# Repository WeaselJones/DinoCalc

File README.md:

DinoCalculator Version 1.0

Download updates from:
http://code.google.com/p/dinocalc/

Summary:
When I was younger I had a calculator that did not have a LCD display but instead had two LED lights, one green and one red.  You would enter a math problem with what you thought the correct answer was (for example, 12 + 12 = 24, and then press the "?" key).  If your answer was right the green LED would light up, if your answer was wrong, the red LED would light up.

This is my salute to that toy from my childhood, as well as a great way for me to engineer and program a neat little project that my preschool son can actually use to check his simple math.

This first part will document the prototype that I have built.  My first objective was to create a calculator capable of just adding and subtracting using off the shelf items.  I plan on starting with an Arduino Pro Mini for the developmental and prototype stage and once I can get most of the major bugs worked out I will then move on to a final version that has a lower cost and device count (ATmega328p on a custom PCB).  

Future objectives (not in any particular order) will be to:

1) Replace the Arduino Pro Mini board with a custom made PCB and reduce parts to a minimum to lower costs (I already have several friends wanting versions for their kids)

2) Add multiplication and division to the calculator's capabilities (low priority for me since this will involve more keys then a 4x4 matrix keypad and my son is only starting addition and subtraction right now)

3) Develop a custom keypad (maybe using tactile buttons and caps, or making my own "membrane" type keypad, or exploring "conductive" type buttons)

4) Add sound for errors or beep whenever custom keypad button is pressed

5) Develop code so that it could also be used for a "math" type game for multiple players. For example, Display a math problem and contestants enter answer on their calculators. If their answer is right, their token moves away from some peril (like a chomping dinosaur) and if wrong moves closer to peril. Loser is the one that gets eaten (chomp,chomp,chomp)

6) Make the circuit low-power for longer battery life and replace the 9V battery with two NiMH AA batteries or perhaps even a button cell rechargeable battery

7) Add a recharging circuit to recharge the rechargeable batteries from USB

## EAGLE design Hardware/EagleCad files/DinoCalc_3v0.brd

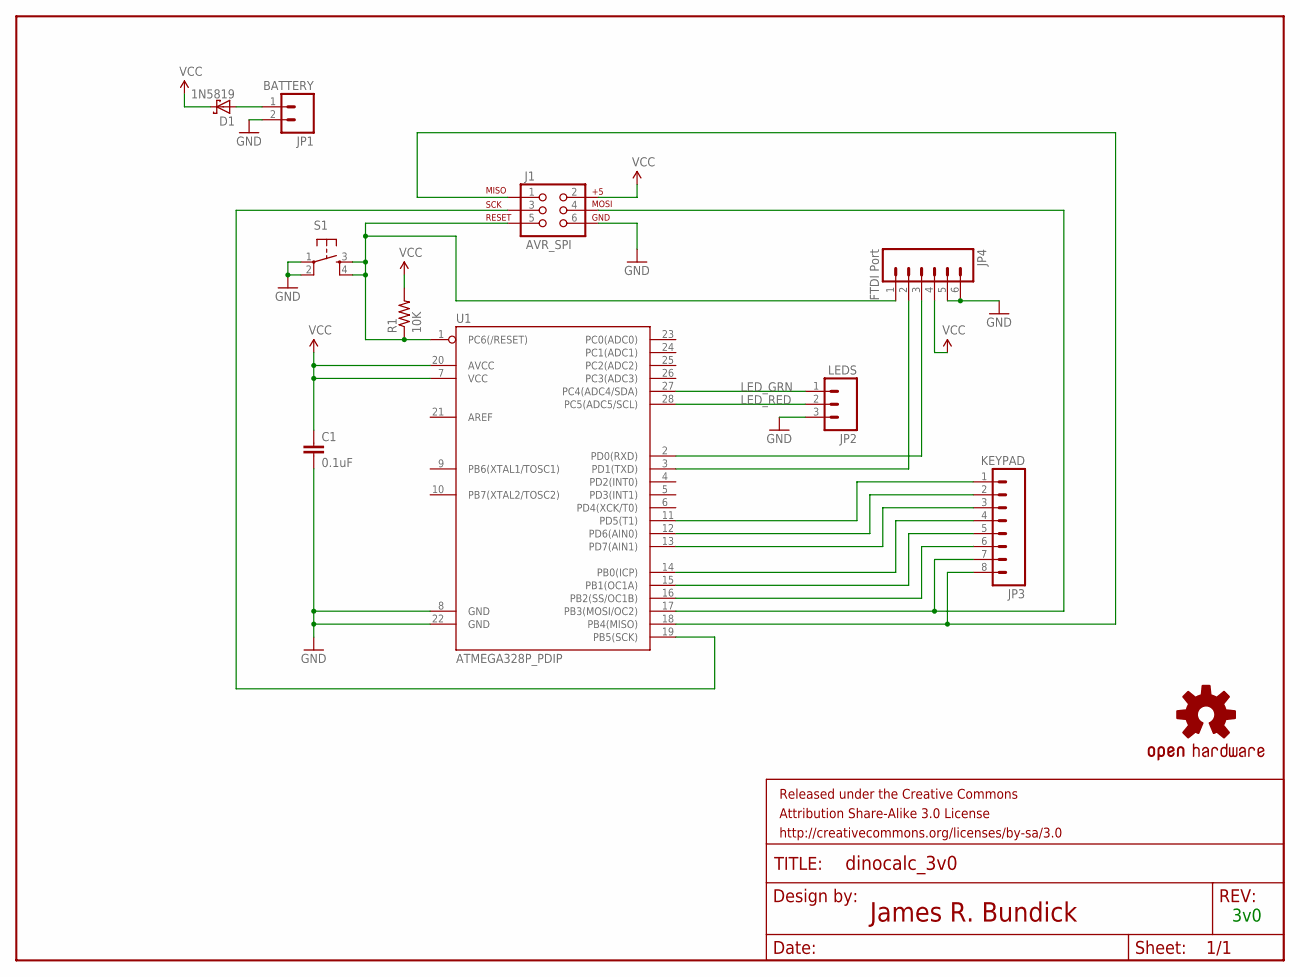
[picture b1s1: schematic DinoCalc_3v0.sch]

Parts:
C1: 0.1uF; CAP-PTH-SMALL
D1: 1N5819; CB417-15
FRAME1: FRAME-LETTER; CREATIVE_COMMONS
J1: AVR_SPI; 2X3_OFFSET
JP1: BATTERY; 1X02
JP2: LEDS; 1X03
JP3: KEYPAD; 1X08
JP4: FTDI Port; 1X06_LONGPADS
LOGO1: OSHW-LOGOL; OSHW-LOGO-L
R1: 10K; AXIAL-0.4
S1: TAC_SWITCHPTH; TACTILE-PTH
U1: ATMEGA328P_PDIP; DIL28-3

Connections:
GND: C1.2, J1.6, JP1.2, JP2.3, JP4.5, JP4.6, S1.1, S1.2, U1.8 (GND), U1.22 (GND)
LED_GRN: JP2.1, U1.27 (PC4(ADC4/SDA))
LED_RED: JP2.2, U1.28 (PC5(ADC5/SCL))
unnamed: JP4.3, U1.2 (PD0(RXD))
unnamed: JP4.2, U1.3 (PD1(TXD))
unnamed: JP3.1, U1.11 (PD5(T1))
unnamed: JP3.2, U1.12 (PD6(AIN0))
unnamed: JP3.3, U1.13 (PD7(AIN1))
unnamed: JP3.4, U1.14 (PB0(ICP))
unnamed: JP3.5, U1.15 (PB1(OC1A))
unnamed: JP3.6, U1.16 (PB2(SS/OC1B))
unnamed: J1.4, JP3.7, U1.17 (PB3(MOSI/OC2))
unnamed: J1.1, JP3.8, U1.18 (PB4(MISO))
unnamed: D1.A, JP1.1
unnamed: J1.5, JP4.1, R1.P$1 (1), S1.3, S1.4, U1.1 (PC6(/RESET))
unnamed: J1.3, U1.19 (PB5(SCK))
VCC: C1.1, D1.C, J1.2, JP4.4, R1.P$2 (2), U1.7 (VCC), U1.20 (AVCC)

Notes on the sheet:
3v0

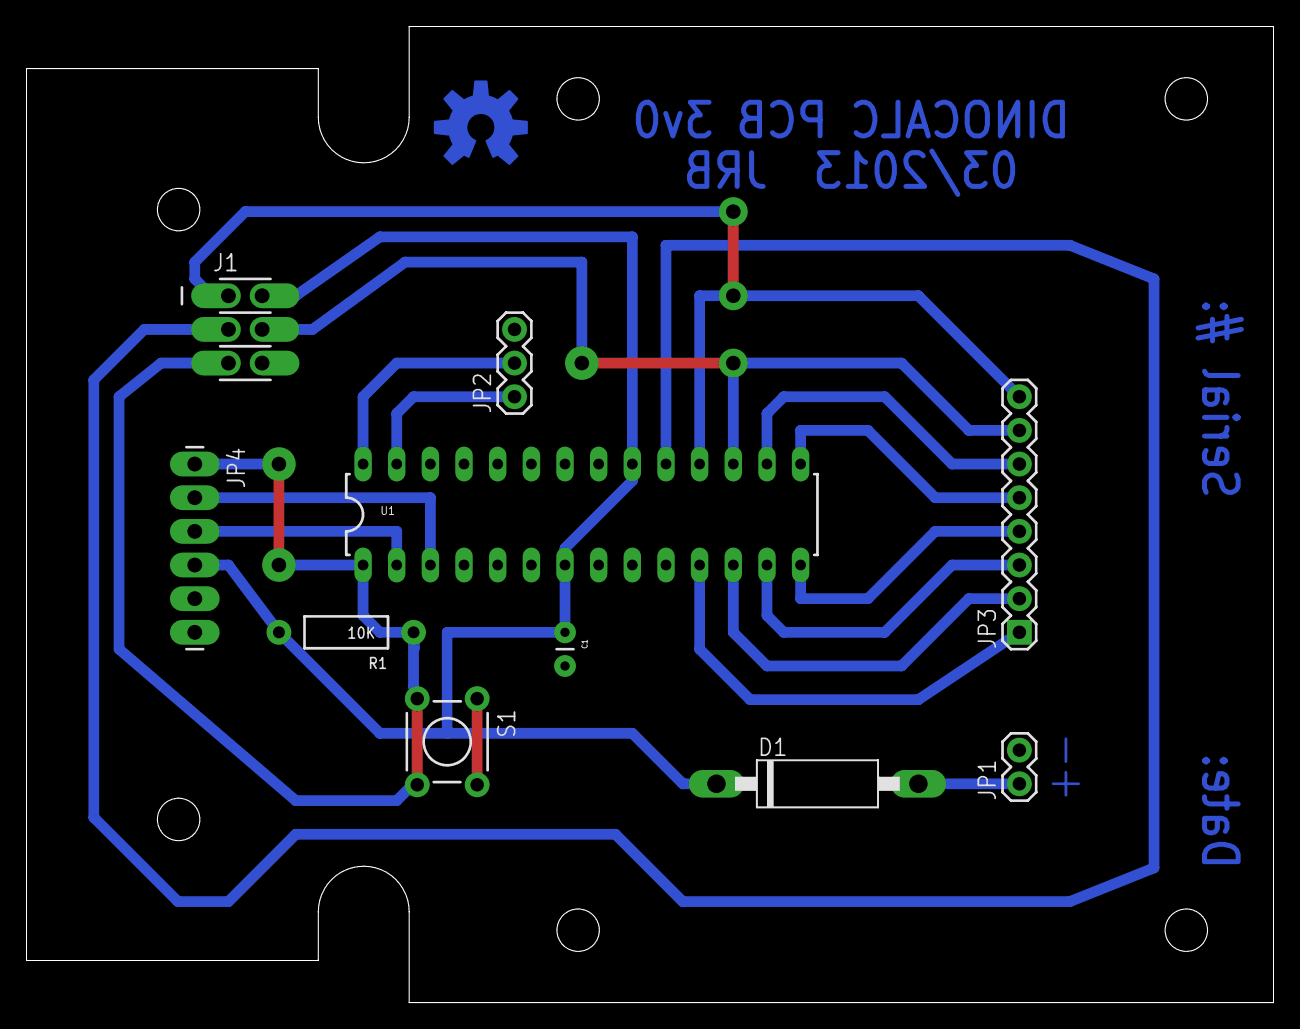
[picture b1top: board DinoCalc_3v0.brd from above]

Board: 2 copper layers, 94.1 x 73.7 mm, 12 parts (0 on the bottom side), 17 nets.

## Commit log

2013-01-04 readme
2013-01-04 first version. Getting keypad to work
2013-01-04 Update Software/Quiz_Kid_Clone_0v1/Quiz_Kid_Clone_0v1.ino
    Minor typo in comment
2013-01-04 Name Change to DinoCalc
2013-01-04 removed version number from name
    still learning git
2013-01-04 conversion of strings to integers
2013-01-04 Bill of Material link to Mouser.com
2013-01-04 Working Version with Integers Only
2013-01-04 Ready for Release
    Floating Numbers, Decimals, and negative numbers can be added or
    subtracted now.
2013-01-04 added email to comments
2013-01-04 hex file of code version 1.0
2013-01-07 Create Sparkfun BOM
2013-01-07 Update Hardware/Sparkfun BOM
2013-01-07 mark for deletion.... replaced by sparkfun bom.txt
2013-01-08 file replaced
2013-01-08 Update of Hardware Files
2013-01-08 Corrected misspelled word
2013-01-08 Combined Bill of Materials into one text file
2013-01-08 Added to comments
2013-01-08 changed extention of readme to txt
2013-01-08 Revert "trying "roll back" commit"
    This reverts commit 63c8c73e9d43efcebebcaa887f6a1c7d872b2b6e.
2013-01-08 Revert "Create test.txt"
    This reverts commit c5edeb639a634842aa80e8ce6842556e8ed67f2d.
2013-01-08 Change Comment
2013-01-08 Revert "Change Comment"
    This reverts commit 6f42fae5289495b0df5cc24554d48e8b1769a4fd.
2013-01-10 Low Power Code Added
    Code ported to an Atmega Chip running at 8MHz and
    2.7 V
2013-01-10 Adding placeholders for Eagle Files of the PCB
2013-01-10 Rename of Directory
2013-01-10 Start of the PCB
2013-01-12 Ready to etch for testing
2013-01-13 Added diode
    Diode added for reverse battery protection. Also optimized placement of
    components a little bit.
2013-01-13 Created a BOM folder
    BOM folder created for different versions of DinoCalc
2013-01-13 Create a inlay folder
    The inlay folder will be were the example inlays are placed
2013-01-13 Updated Comments
    Reference to Nick Gammon added and BOM removed from software comments
    since it is now an external file.
2013-01-13 Updated Version Numbering
2013-01-14 Added Date Made and Serial # Labeling to PCB
2013-01-14 Convert from .rft to .txt
2013-01-14 Create Layouts
2013-01-15 Create New Hardware Layout Inkscape files
2013-01-15 roll back
2013-01-15 Trying to get back in sync
2013-01-15 added .gitignore and .gitattributes
2013-01-15 moved file to bom
2013-01-15 Added Hardware Layout Version 1v0
2013-01-15 Version 1.0 Release
2013-01-15 Another Merge
2013-01-16 Version 1.1 Work in Progress
    Trying to incorporate Low Power Usage into the code
2013-01-16 Updated Readme and changed extension to txt
2013-01-16 Adding Licenses.txt
2013-01-18 Added Protoboard/Enclosure Kit Datasheet
    Datasheet has Protoboard picture at actual size
2013-01-24 Updates to txt files
2013-01-24 Update to BOM 1v0
2013-01-24 Revert "Create Test REadme.md"
    This reverts commit 5fbad9ea9879a6f4b0af6c0b2187289635bc24c9.
2013-03-08 Renamed T-rex inlay, added fairy inlay, added inlay tutorial
2013-03-11 Reorganized Files and Updated BOM
2013-03-11 Add EagleCad Schematic for Hardware version 1
2013-03-11 Moved "Make Your Own DinoCalc Inlay.pdf" to DinoCalc Inlays folder
2013-03-11 Updated Software Comments
    Changed "Arduino pin 2" thru "Arduino pin 11" to "Arduino D 2" thru
    "Arduino D11" to prevent confusion with digital pin 2 on the Arduino and
    actual pin 2 on the Atmega 328P chip.
2013-03-11 Recompiled DinoCalc hex file
2013-03-11 Attached version numbers to software files
2013-03-11 Added png picture of EagleCad Schematic
    For people without EagleCad
2013-03-11 Created pdf of EagleCad Schematic
2013-03-12 Added Version History File
2013-03-12 Rename Software Files
2013-03-13 Add BOM for version 2.0 of Hardware
    Protoboard with Atmega328p
2013-03-13 Added Version 2v0 of Hardware Layout
2013-03-13 Added Inkscape file for Hardware Layout 2v0
2013-03-13 Added Description of different Hardware Versions
2013-03-13 Added BOM file for Hardware 3.0
2013-03-13 Updated BOM for Hardware 2.0
2013-03-13 Add EagleCad files for Hardware 3.0
2013-03-13 Renamed Hardware Layouts folder to ProtoBoard Layouts
2013-03-13 Rename Hardware Layout files to ProtoBoard Layout
2013-03-13 Renamed Inkscape Layout files
    Renamed Layout files from "Hardware Layout" to "Protoboard" Layout
2013-03-13 Rename hex file to 1v0
    added 1v0 to hex file name so I'll remember this is the initial code
2013-03-13 Software 1v1: Added Low Power Code
    Code still needs work
2013-03-13 Added WIP notes.txt
    Work in Progress Notes
2013-03-19 Added DinoCalc Software version 2.0alpha
2013-03-19 Housekeeping on code
    Minor modifications

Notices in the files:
parts and their libraries:
SparkFun-DigitalIC: Licensing: CC v3.0 Share-Alike You are welcome to use this library for commercial purposes.
SparkFun-Aesthetics: Released under the Creative Commons Attribution Share-Alike 3.0 License
SparkFun-Aesthetics: http://creativecommons.org/licenses/by-sa/3.0
